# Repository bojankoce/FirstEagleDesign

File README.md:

# FirstEagleDesign
My First Eagle Design on GIT

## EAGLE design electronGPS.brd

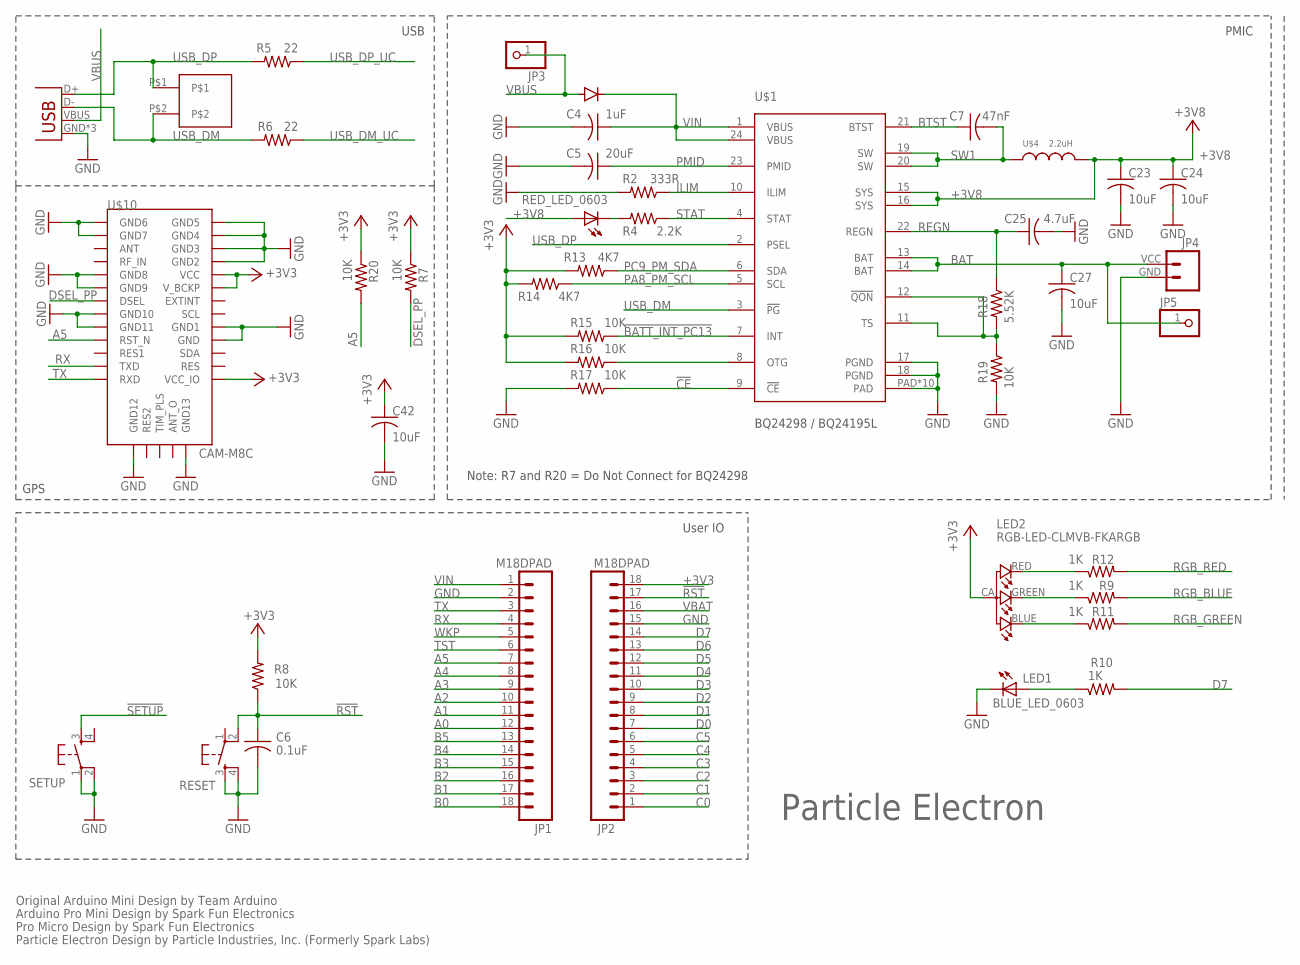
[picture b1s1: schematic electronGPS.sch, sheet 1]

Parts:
BLUE_LED_0603: LEDNOSILK; LED-0603-NS
C4: 1uF; C0603_B
C5: 20uF; C0603_B
C6: 0.1uF; C0402_B
C7: 47nF; C0402_B
C23, C24, C27, C42: 10uF; C0603_B
C25: 4.7uF; C0603_B
JP1, JP2: M18DPAD; 1X18-D-PADS
JP3, JP5: PINHD-1X1NOSILK; 1X01_NO_SILK
JP4: M024UCON-15767; JST-2-SMD-VERT
LED2: RGB-LED-CLMVB-FKARGB; PLCC4-2MM-RGB
R2: 333R; R0402_B
R4: 2.2K; R0402_B
R5, R6: 22; R0402_B
R7, R8, R15, R16, R17, R19, R20: 10K; R0402_B
R9, R10, R11, R12: 1K; R0402_B
R13, R14: 4K7; R0402_B
R18: 5.52K; R0402_B
RED_LED_0603: LED0603; LED-0603
RESET: KMR211GLFS; TACTILE_SWITCH_SMD
SETUP: KMR211GLFS; TACTILE_SWITCH_SMD
U$1: BQ24298 / BQ24195L; QFN24
U$3: DIODE_NT; DIODE-DO-220AA_NT(SMP)
U$4: 2.2uH; 4020TYPE_NT
U$7: M02_0.05_HEADER
U$10: CAM-M8C; CAM-MC
X1: USB-MICROB; USB-MICROB-SLOT-HOLE

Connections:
!BATT_INT_PC13: R15.1, U$1.7 (INT); also elsewhere on the board
!CE: R17.1, U$1.9 (!CE)
!RST: C6.1, JP2.17, R8.1, RESET.2; also elsewhere on the board
!SETUP: SETUP.3; also elsewhere on the board
+3V3: C42.1, JP2.18, LED2.CA (1), R7.1, R8.2, R13.2, R14.2, R15.2, R16.2, R20.1, U$10.P$1 (VCC_IO), U$10.P$8 (V_BCKP), U$10.P$9 (VCC); also elsewhere on the board
+3V8: C23.1, C24.1, RED_LED_0603.A, U$1.15 (SYS), U$1.16 (SYS), U$4.P$2 (2); also elsewhere on the board
A0: JP1.12; also elsewhere on the board
A1: JP1.11; also elsewhere on the board
A2: JP1.10; also elsewhere on the board
A3: JP1.9; also elsewhere on the board
A4: JP1.8; also elsewhere on the board
A5: JP1.7, R20.2, U$10.P$23 (RST_N); also elsewhere on the board
B0: JP1.18; also elsewhere on the board
B1: JP1.17; also elsewhere on the board
B2: JP1.16; also elsewhere on the board
B3: JP1.15; also elsewhere on the board
B4: JP1.14; also elsewhere on the board
B5: JP1.13; also elsewhere on the board
BAT: C27.1, JP4.VCC (2), JP5.1, U$1.13 (BAT), U$1.14 (BAT); also elsewhere on the board
BTST: C7.1, U$1.21 (BTST)
C0: JP2.1; also elsewhere on the board
C1: JP2.2; also elsewhere on the board
C2: JP2.3; also elsewhere on the board
C3: JP2.4; also elsewhere on the board
C4: JP2.5; also elsewhere on the board
C5: JP2.6; also elsewhere on the board
D0: JP2.7; also elsewhere on the board
D1: JP2.8; also elsewhere on the board
D2: JP2.9; also elsewhere on the board
D3: JP2.10; also elsewhere on the board
D4: JP2.11; also elsewhere on the board
D5: JP2.12; also elsewhere on the board
D6: JP2.13; also elsewhere on the board
D7: JP2.14, R10.2; also elsewhere on the board
DSEL_PP: R7.2, U$10.P$20 (DSEL)
GND: BLUE_LED_0603.C, C4.2, C5.2, C6.2, C23.2, C24.2, C25.2, C27.2, C42.2, JP1.2, JP2.15, JP4.GND (1), R2.2, R17.2, R19.2, RESET.3, RESET.4, SETUP.1, SETUP.2, U$1.17 (PGND), U$1.18 (PGND), U$1.PAD, U$1.PAD@1 (PAD), U$1.PAD@2 (PAD), U$1.PAD@3 (PAD), U$1.PAD@4 (PAD), U$1.PAD@5 (PAD), U$1.PAD@6 (PAD), U$1.PAD@7 (PAD), U$1.PAD@8 (PAD), U$1.PAD@9 (PAD), U$10.P$4 (GND), U$10.P$5 (GND1), U$10.P$10 (GND2), U$10.P$11 (GND3), U$10.P$12 (GND4), U$10.P$13 (GND5), U$10.P$14 (GND6), U$10.P$15 (GND7), U$10.P$18 (GND8), U$10.P$19 (GND9), U$10.P$21 (GND10), U$10.P$22 (GND11), U$10.P$27 (GND12), U$10.P$31 (GND13), X1.GND, X1.MT1 (GND), X1.MT2 (GND); also elsewhere on the board
ILIM: R2.1, U$1.10 (ILIM)
LED1: BLUE_LED_0603.A, R10.1
unnamed: R4.2, RED_LED_0603.C
unnamed: R16.1, U$1.8 (OTG)
unnamed: LED2.BLUE (2), R11.1
unnamed: LED2.GREEN (3), R9.1
unnamed: LED2.RED (4), R12.1
PA8_PM_SCL: R14.1, U$1.5 (SCL); also elsewhere on the board
PC9_PM_SDA: R13.1, U$1.6 (SDA); also elsewhere on the board
PMID: C5.1, U$1.23 (PMID)
REGN: C25.1, R18.1, U$1.22 (REGN)
RGB_BLUE: R11.2; also elsewhere on the board
RGB_GREEN: R9.2; also elsewhere on the board
RGB_RED: R12.2; also elsewhere on the board
RX: JP1.4, U$10.P$25 (TXD); also elsewhere on the board
STAT: R4.1, U$1.4 (STAT)
SW1: C7.2, U$1.19 (SW), U$1.20 (SW), U$4.P$1 (1)
TS: R18.2, R19.1, U$1.11 (TS), U$1.12 (!QON)
TST: JP1.6; also elsewhere on the board
TX: JP1.3, U$10.P$26 (RXD); also elsewhere on the board
USB_DM: R6.2, U$1.3 (!PG), U$7.P$2, X1.D-
USB_DM_UC: R6.1; also elsewhere on the board
USB_DP: R5.2, U$1.2 (PSEL), U$7.P$1, X1.D+
USB_DP_UC: R5.1; also elsewhere on the board
VBAT: JP2.16; also elsewhere on the board
VBUS: JP3.1, U$3.ANODE, X1.VBUS
VIN: C4.1, JP1.1, U$1.1 (VBUS), U$1.24 (VBUS), U$3.CATHODE
WKP: JP1.5; also elsewhere on the board

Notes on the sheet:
PMIC
User IO
USB
Particle Electron
Note: R7 and R20 = Do Not Connect for BQ24298
Original Arduino Mini Design by Team Arduino
Arduino Pro Mini Design by Spark Fun Electronics
Pro Micro Design by Spark Fun Electronics
Particle Electron Design by Particle Industries, Inc. (Formerly Spark Labs)
GPS

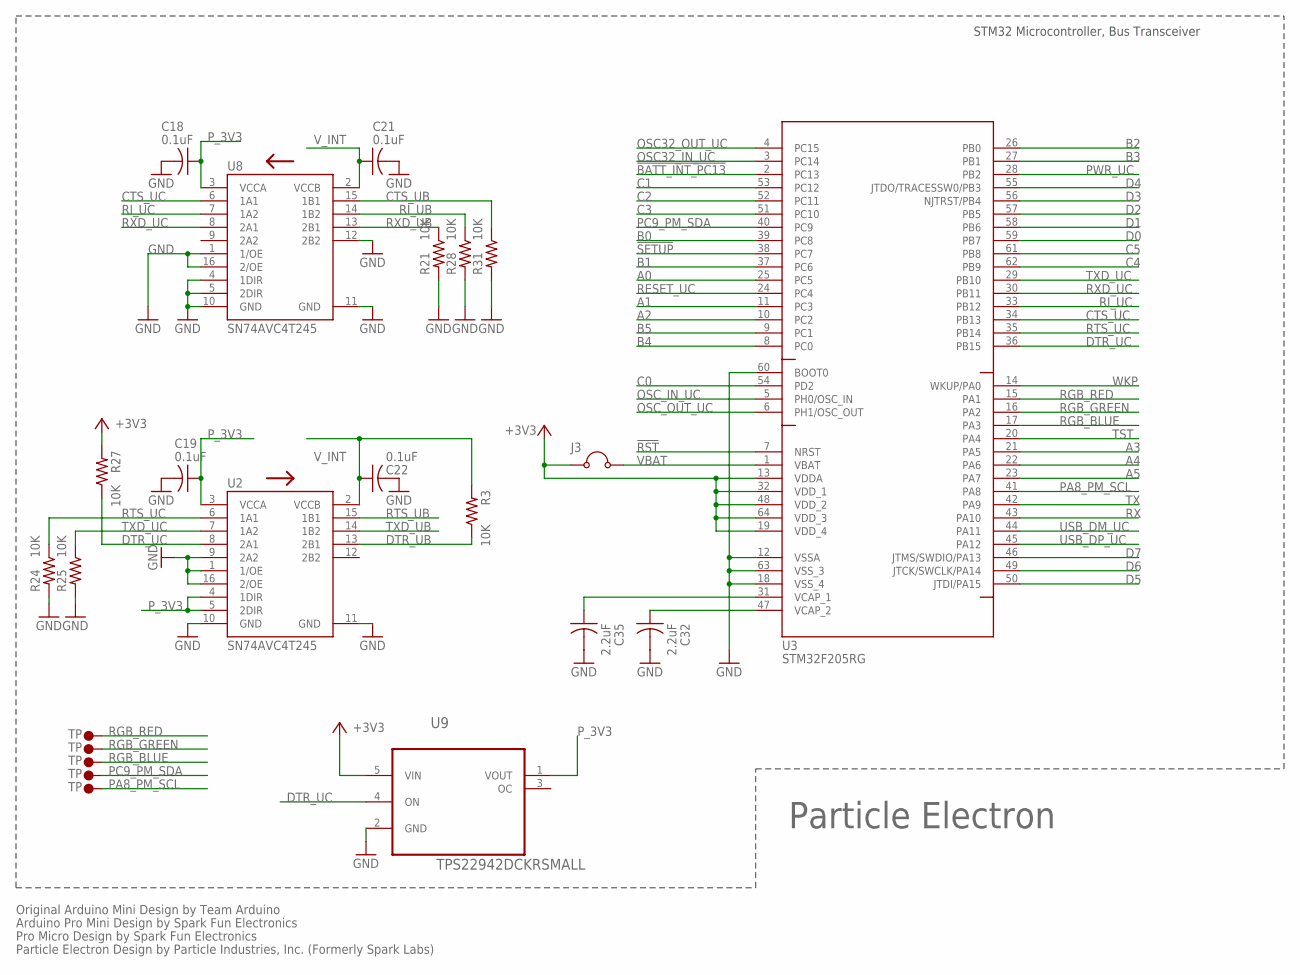
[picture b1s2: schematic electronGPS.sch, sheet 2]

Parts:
C18, C19, C21, C22: 0.1uF; C0402_B
C32, C35: 2.2uF; C0402_B
J3: JUMPER_NC_SMD; JUMPER_SMD_NC
R3, R21, R24, R25, R27, R28, R31: 10K; R0402_B
U2, U8: SN74AVC4T245; UFQFN-16
U3: STM32F205RG; LQFP64
U9: TPS22942DCKRSMALL; SC70-5
U$8, U$9, U$11, U$12, U$13: TP0; TP30_BOT

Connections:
!BATT_INT_PC13: U3.2 (PC13); also elsewhere on the board
!RST: U3.7 (NRST); also elsewhere on the board
!SETUP: U3.38 (PC7); also elsewhere on the board
+3V3: J3.1, R27.2, U3.13 (VDDA), U3.19 (VDD_4), U3.32 (VDD_1), U3.48 (VDD_2), U3.64 (VDD_3), U9.5 (VIN); also elsewhere on the board
A0: U3.25 (PC5); also elsewhere on the board
A1: U3.11 (PC3); also elsewhere on the board
A2: U3.10 (PC2); also elsewhere on the board
A3: U3.21 (PA5); also elsewhere on the board
A4: U3.22 (PA6); also elsewhere on the board
A5: U3.23 (PA7); also elsewhere on the board
B0: U3.39 (PC8); also elsewhere on the board
B1: U3.37 (PC6); also elsewhere on the board
B2: U3.26 (PB0); also elsewhere on the board
B3: U3.27 (PB1); also elsewhere on the board
B4: U3.8 (PC0); also elsewhere on the board
B5: U3.9 (PC1); also elsewhere on the board
C0: U3.54 (PD2); also elsewhere on the board
C1: U3.53 (PC12); also elsewhere on the board
C2: U3.52 (PC11); also elsewhere on the board
C3: U3.51 (PC10); also elsewhere on the board
C4: U3.62 (PB9); also elsewhere on the board
C5: U3.61 (PB8); also elsewhere on the board
CTS_UB: R31.1, U8.15 (1B1); also elsewhere on the board
CTS_UC: U3.34 (PB13), U8.6 (1A1)
D0: U3.59 (PB7); also elsewhere on the board
D1: U3.58 (PB6); also elsewhere on the board
D2: U3.57 (PB5); also elsewhere on the board
D3: U3.56 (NJTRST/PB4); also elsewhere on the board
D4: U3.55 (JTDO/TRACESSW0/PB3); also elsewhere on the board
D5: U3.50 (JTDI/PA15); also elsewhere on the board
D6: U3.49 (JTCK/SWCLK/PA14); also elsewhere on the board
D7: U3.46 (JTMS/SWDIO/PA13); also elsewhere on the board
DTR_UB: R3.1, U2.13 (2B1); also elsewhere on the board
DTR_UC: R27.1, U2.8 (2A1), U3.36 (PB15), U9.4 (ON)
GND: C18.2, C19.2, C21.2, C22.2, C32.2, C35.2, R21.2, R24.2, R25.2, R28.2, R31.2, U2.1 (1/OE), U2.9 (2A2), U2.10 (GND), U2.11 (GND), U2.16 (2/OE), U3.12 (VSSA), U3.18 (VSS_4), U3.60 (BOOT0), U3.63 (VSS_3), U8.1 (1/OE), U8.4 (1DIR), U8.5 (2DIR), U8.10 (GND), U8.11 (GND), U8.12 (2B2), U8.16 (2/OE), U9.2 (GND); also elsewhere on the board
unnamed: C35.1, U3.31 (VCAP_1)
unnamed: C32.1, U3.47 (VCAP_2)
OSC32_IN_UC: U3.3 (PC14); also elsewhere on the board
OSC32_OUT_UC: U3.4 (PC15); also elsewhere on the board
OSC_IN_UC: U3.5 (PH0/OSC_IN); also elsewhere on the board
OSC_OUT_UC: U3.6 (PH1/OSC_OUT); also elsewhere on the board
PA8_PM_SCL: U3.41 (PA8), U$9.P$1; also elsewhere on the board
PC9_PM_SDA: U3.40 (PC9), U$8.P$1; also elsewhere on the board
PWR_UC: U3.28 (PB2); also elsewhere on the board
P_3V3: C18.1, C19.1, U2.3 (VCCA), U2.4 (1DIR), U2.5 (2DIR), U8.3 (VCCA), U9.1 (VOUT)
RESET_UC: U3.24 (PC4); also elsewhere on the board
RGB_BLUE: U3.17 (PA3), U$13.P$1; also elsewhere on the board
RGB_GREEN: U3.16 (PA2), U$12.P$1; also elsewhere on the board
RGB_RED: U3.15 (PA1), U$11.P$1; also elsewhere on the board
RI_UB: R28.1, U8.14 (1B2); also elsewhere on the board
RI_UC: U3.33 (PB12), U8.7 (1A2)
RTS_UB: U2.15 (1B1); also elsewhere on the board
RTS_UC: R24.1, U2.6 (1A1), U3.35 (PB14)
RX: U3.43 (PA10); also elsewhere on the board
RXD_UB: R21.1, U8.13 (2B1); also elsewhere on the board
RXD_UC: U3.30 (PB11), U8.8 (2A1)
TST: U3.20 (PA4); also elsewhere on the board
TX: U3.42 (PA9); also elsewhere on the board
TXD_UB: U2.14 (1B2); also elsewhere on the board
TXD_UC: R25.1, U2.7 (1A2), U3.29 (PB10)
USB_DM_UC: U3.44 (PA11); also elsewhere on the board
USB_DP_UC: U3.45 (PA12); also elsewhere on the board
VBAT: J3.2, U3.1 (VBAT); also elsewhere on the board
V_INT: C21.1, C22.1, R3.2, U2.2 (VCCB), U8.2 (VCCB); also elsewhere on the board
WKP: U3.14 (WKUP/PA0); also elsewhere on the board

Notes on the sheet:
Particle Electron
STM32 Microcontroller, Bus Transceiver
Original Arduino Mini Design by Team Arduino
Arduino Pro Mini Design by Spark Fun Electronics
Pro Micro Design by Spark Fun Electronics
Particle Electron Design by Particle Industries, Inc. (Formerly Spark Labs)

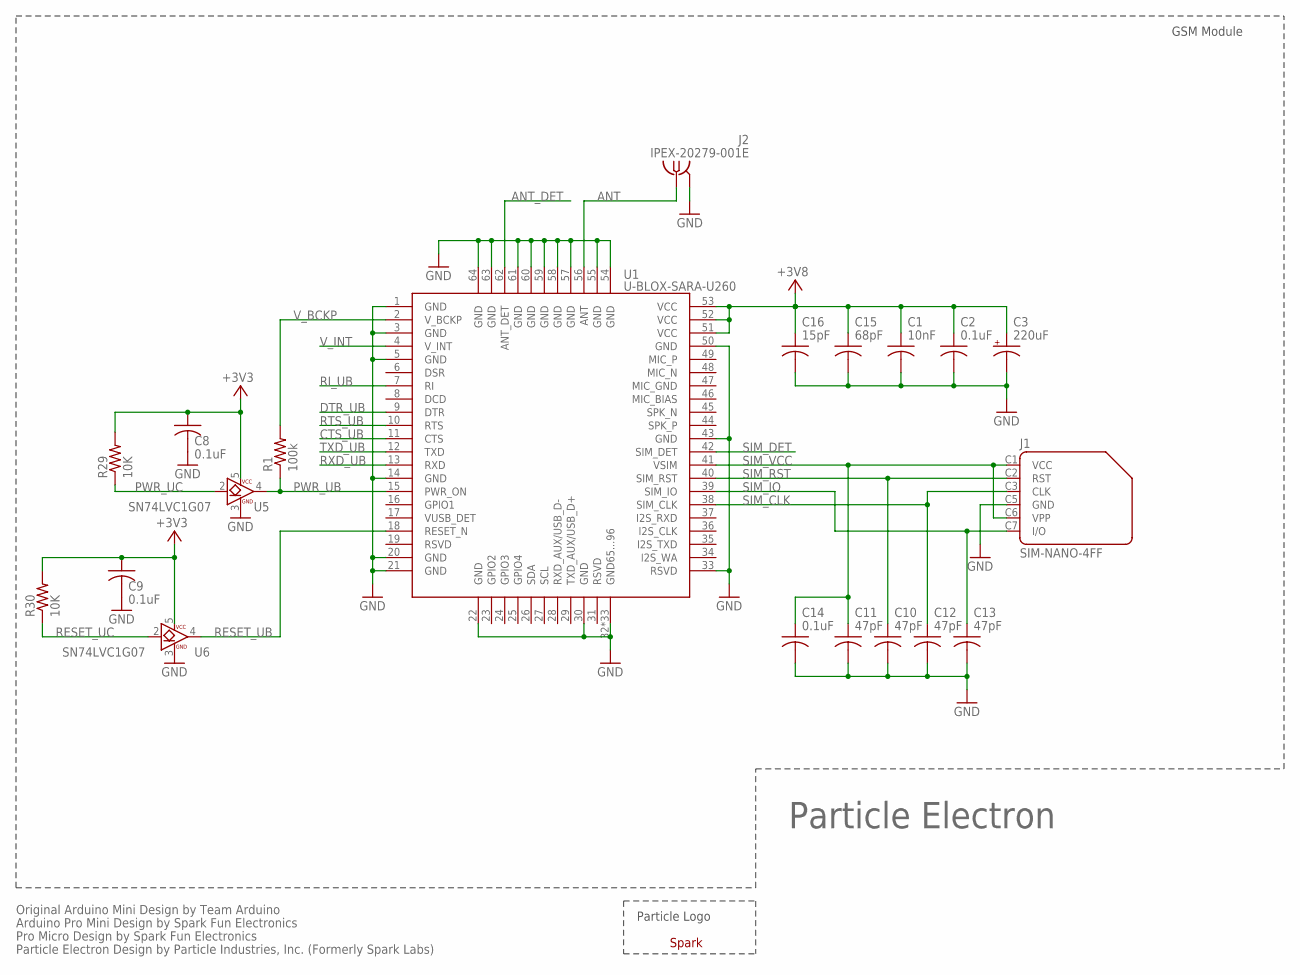
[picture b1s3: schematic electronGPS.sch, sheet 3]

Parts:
C1: 10nF; C0402_B
C2, C8, C9, C14: 0.1uF; C0402_B
C3: 220uF; C/6032-28R
C10, C11, C12, C13: 47pF; C0402_B
C15: 68pF; C0402_B
C16: 15pF; C0402_B
J1: SIM-NANO-4FF; GCT-SIM8100
J2: IPEX-20279-001E
R1: 100k; R0402_B
R29, R30: 10K; R0402_B
U1: U-BLOX-SARA-U260; U-BLOX-SARA-U2
U5, U6: SN74LVC1G07; SC-70-5
U$2: SPARK_LOGO2

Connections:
+3V3: C8.1, C9.1, R29.2, R30.2, U5.5 (VCC), U6.5 (VCC); also elsewhere on the board
+3V8: C1.1, C2.1, C3.+, C15.1, C16.1, U1.51 (VCC), U1.52 (VCC), U1.53 (VCC); also elsewhere on the board
ANT: J2.1, U1.56 (ANT)
ANT_DET: U1.62 (ANT_DET)
CTS_UB: U1.11 (CTS); also elsewhere on the board
DTR_UB: U1.9 (DTR); also elsewhere on the board
GND: C1.2, C2.2, C3.-, C8.2, C9.2, C10.2, C11.2, C12.2, C13.2, C14.2, C15.2, C16.2, J1.C5 (GND), J2.2@1 (GND), J2.2@2 (GND), U1.1 (GND), U1.3 (GND), U1.5 (GND), U1.14 (GND), U1.20 (GND), U1.21 (GND), U1.22 (GND), U1.30 (GND), U1.32 (GND65...96), U1.33 (RSVD), U1.43 (GND), U1.50 (GND), U1.54 (GND), U1.55 (GND), U1.57 (GND), U1.58 (GND), U1.59 (GND), U1.60 (GND), U1.61 (GND), U1.63 (GND), U1.64 (GND), U1.65 (GND65...96), U1.66 (GND65...96), U1.67 (GND65...96), U1.68 (GND65...96), U1.69 (GND65...96), U1.70 (GND65...96), U1.71 (GND65...96), U1.72 (GND65...96), U1.73 (GND65...96), U1.74 (GND65...96), U1.75 (GND65...96), U1.76 (GND65...96), U1.77 (GND65...96), U1.78 (GND65...96), U1.79 (GND65...96), U1.80 (GND65...96), U1.81 (GND65...96), U1.82 (GND65...96), U1.83 (GND65...96), U1.84 (GND65...96), U1.85 (GND65...96), U1.86 (GND65...96), U1.87 (GND65...96), U1.88 (GND65...96), U1.89 (GND65...96), U1.90 (GND65...96), U1.91 (GND65...96), U1.92 (GND65...96), U1.93 (GND65...96), U1.94 (GND65...96), U1.95 (GND65...96), U1.96 (GND65...96), U5.3 (GND), U6.3 (GND); also elsewhere on the board
PWR_UB: R1.1, U1.15 (PWR_ON), U5.4 (B)
PWR_UC: R29.1, U5.2 (A); also elsewhere on the board
RESET_UB: U1.18 (RESET_N), U6.4 (B)
RESET_UC: R30.1, U6.2 (A); also elsewhere on the board
RI_UB: U1.7 (RI); also elsewhere on the board
RTS_UB: U1.10 (RTS); also elsewhere on the board
RXD_UB: U1.13 (RXD); also elsewhere on the board
SIM_CLK: C12.1, J1.C3 (CLK), U1.38 (SIM_CLK)
SIM_DET: U1.42 (SIM_DET)
SIM_IO: C13.1, J1.C7 (I/O), U1.39 (SIM_IO)
SIM_RST: C10.1, J1.C2 (RST), U1.40 (SIM_RST)
SIM_VCC: C11.1, C14.1, J1.C1 (VCC), J1.C6 (VPP), U1.41 (VSIM)
TXD_UB: U1.12 (TXD); also elsewhere on the board
V_BCKP: R1.2, U1.2 (V_BCKP)
V_INT: U1.4 (V_INT); also elsewhere on the board

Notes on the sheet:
Particle Electron
GSM Module
Particle Logo
Original Arduino Mini Design by Team Arduino
Arduino Pro Mini Design by Spark Fun Electronics
Pro Micro Design by Spark Fun Electronics
Particle Electron Design by Particle Industries, Inc. (Formerly Spark Labs)

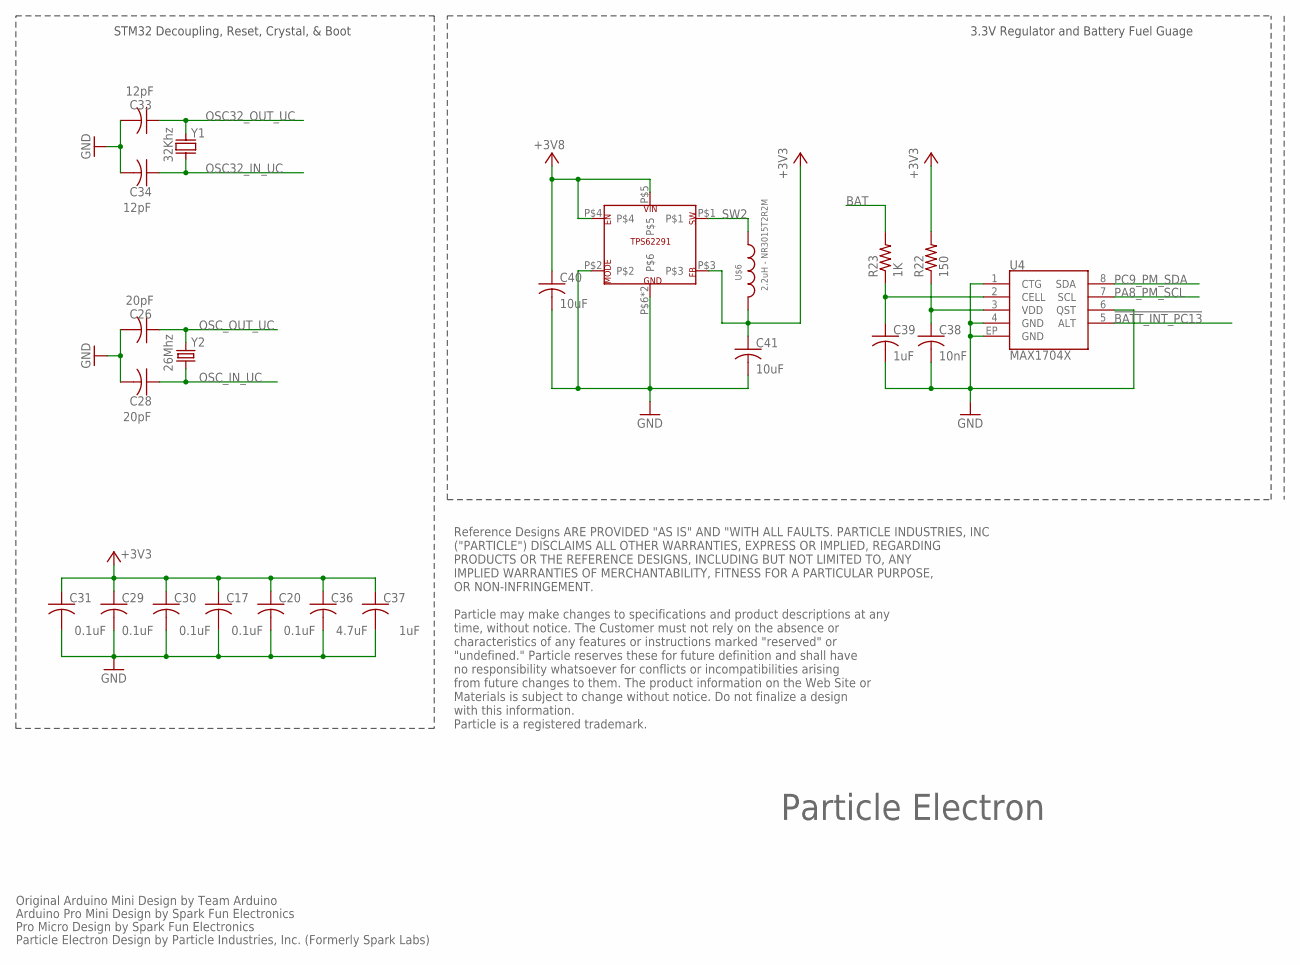
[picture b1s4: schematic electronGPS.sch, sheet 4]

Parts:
C17, C20, C29, C30, C31: 0.1uF; C0402_B
C26, C28: 20pF; C0402_B
C33, C34: 12pF; C0402_B
C36: 4.7uF; C0402_B
C37, C39: 1uF; C0402_B
C38: 10nF; C0402_B
C40, C41: 10uF; C0603_B
R22: 150; 0603-RES
R23: 1K; 0603-RES
U4: MAX1704X; TDFN-8
U$5: TPS62291DRV; S-PWSON-N6
U$6: 2.2uH - NR3015T2R2M; INDUCTOR-NR3015
Y1: 32Khz; FC135
Y2: 26Mhz; CRYSTAL-SMD-5X3

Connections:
!BATT_INT_PC13: U4.5 (ALT); also elsewhere on the board
+3V3: C17.1, C20.1, C29.1, C30.1, C31.1, C36.1, C37.1, C41.1, R22.2, U$5.P$3, U$6.2; also elsewhere on the board
+3V8: C40.1, U$5.P$4, U$5.P$5; also elsewhere on the board
BAT: R23.2; also elsewhere on the board
GND: C17.2, C20.2, C26.2, C28.2, C29.2, C30.2, C31.2, C33.2, C34.2, C36.2, C37.2, C38.2, C39.2, C40.2, C41.2, U4.1 (CTG), U4.4 (GND), U4.6 (QST), U4.EP (GND), U$5.P$2, U$5.P$6, U$5.TP; also elsewhere on the board
unnamed: C39.1, R23.1, U4.2 (CELL)
unnamed: C38.1, R22.1, U4.3 (VDD)
OSC32_IN_UC: C34.1, Y1.X1 (1); also elsewhere on the board
OSC32_OUT_UC: C33.1, Y1.X2 (2); also elsewhere on the board
OSC_IN_UC: C28.1, Y2.1; also elsewhere on the board
OSC_OUT_UC: C26.1, Y2.3 (2); also elsewhere on the board
PA8_PM_SCL: U4.7 (SCL); also elsewhere on the board
PC9_PM_SDA: U4.8 (SDA); also elsewhere on the board
SW2: U$5.P$1, U$6.1

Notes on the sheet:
Particle Electron
STM32 Decoupling, Reset, Crystal, & Boot
3.3V Regulator and Battery Fuel Guage
Original Arduino Mini Design by Team Arduino
Arduino Pro Mini Design by Spark Fun Electronics
Pro Micro Design by Spark Fun Electronics
Particle Electron Design by Particle Industries, Inc. (Formerly Spark Labs)
Reference Designs ARE PROVIDED "AS IS" AND "WITH ALL FAULTS. PARTICLE INDUSTRIES, INC ("PARTICLE") DISCLAIMS ALL OTHER WARRANTIES, EXPRESS OR IMPLIED, REGARDING PRODUCTS OR THE REFERENCE DESIGNS, INCLUDING BUT NOT LIMITED TO, ANY IMPLIED WARRANTIES OF MERCHANTABILITY, FITNESS FOR A PARTICULAR PURPO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

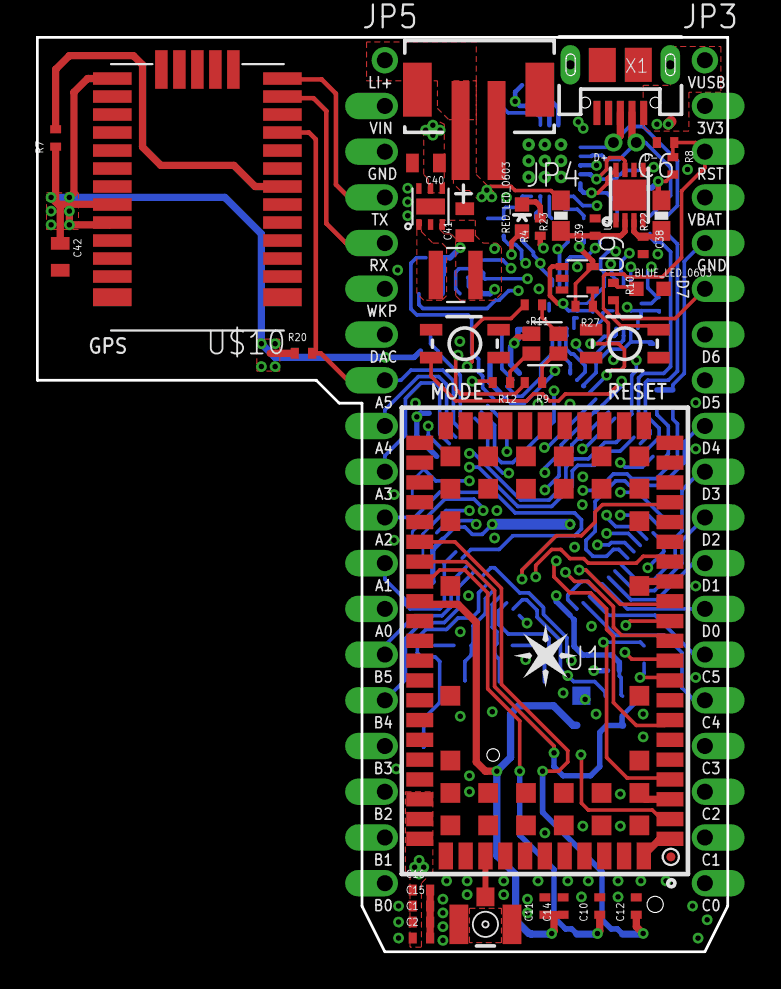
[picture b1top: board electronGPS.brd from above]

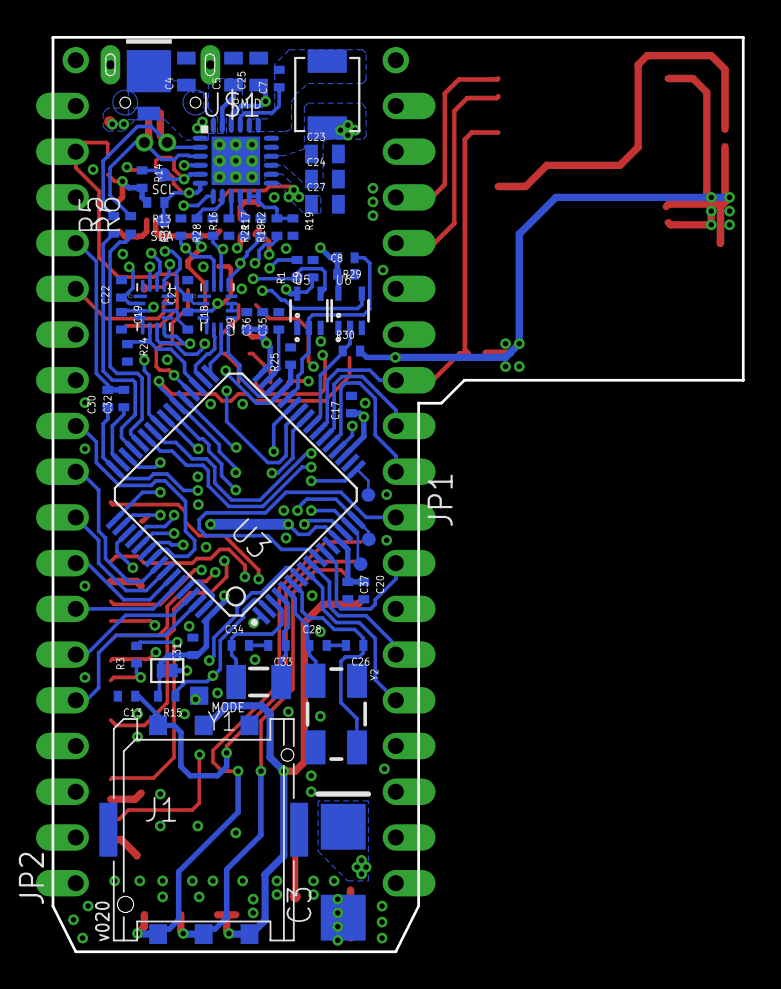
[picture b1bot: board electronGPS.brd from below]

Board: 4 copper layers, 38.4 x 50.8 mm, 109 parts (61 on the bottom side), 97 nets.

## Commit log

2016-04-26 Added files via upload
    .sch and .brd files added

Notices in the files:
parts and their libraries:
SparkFun-FreqCtrl: Licensing: CC v3.0 Share-Alike You are welcome to use this library for commercial purposes.
SparkFun-Connectors: Licensing: Creative Commons ShareAlike 4.0 International - https://creativecommons.org/licenses/by-sa/4.0
